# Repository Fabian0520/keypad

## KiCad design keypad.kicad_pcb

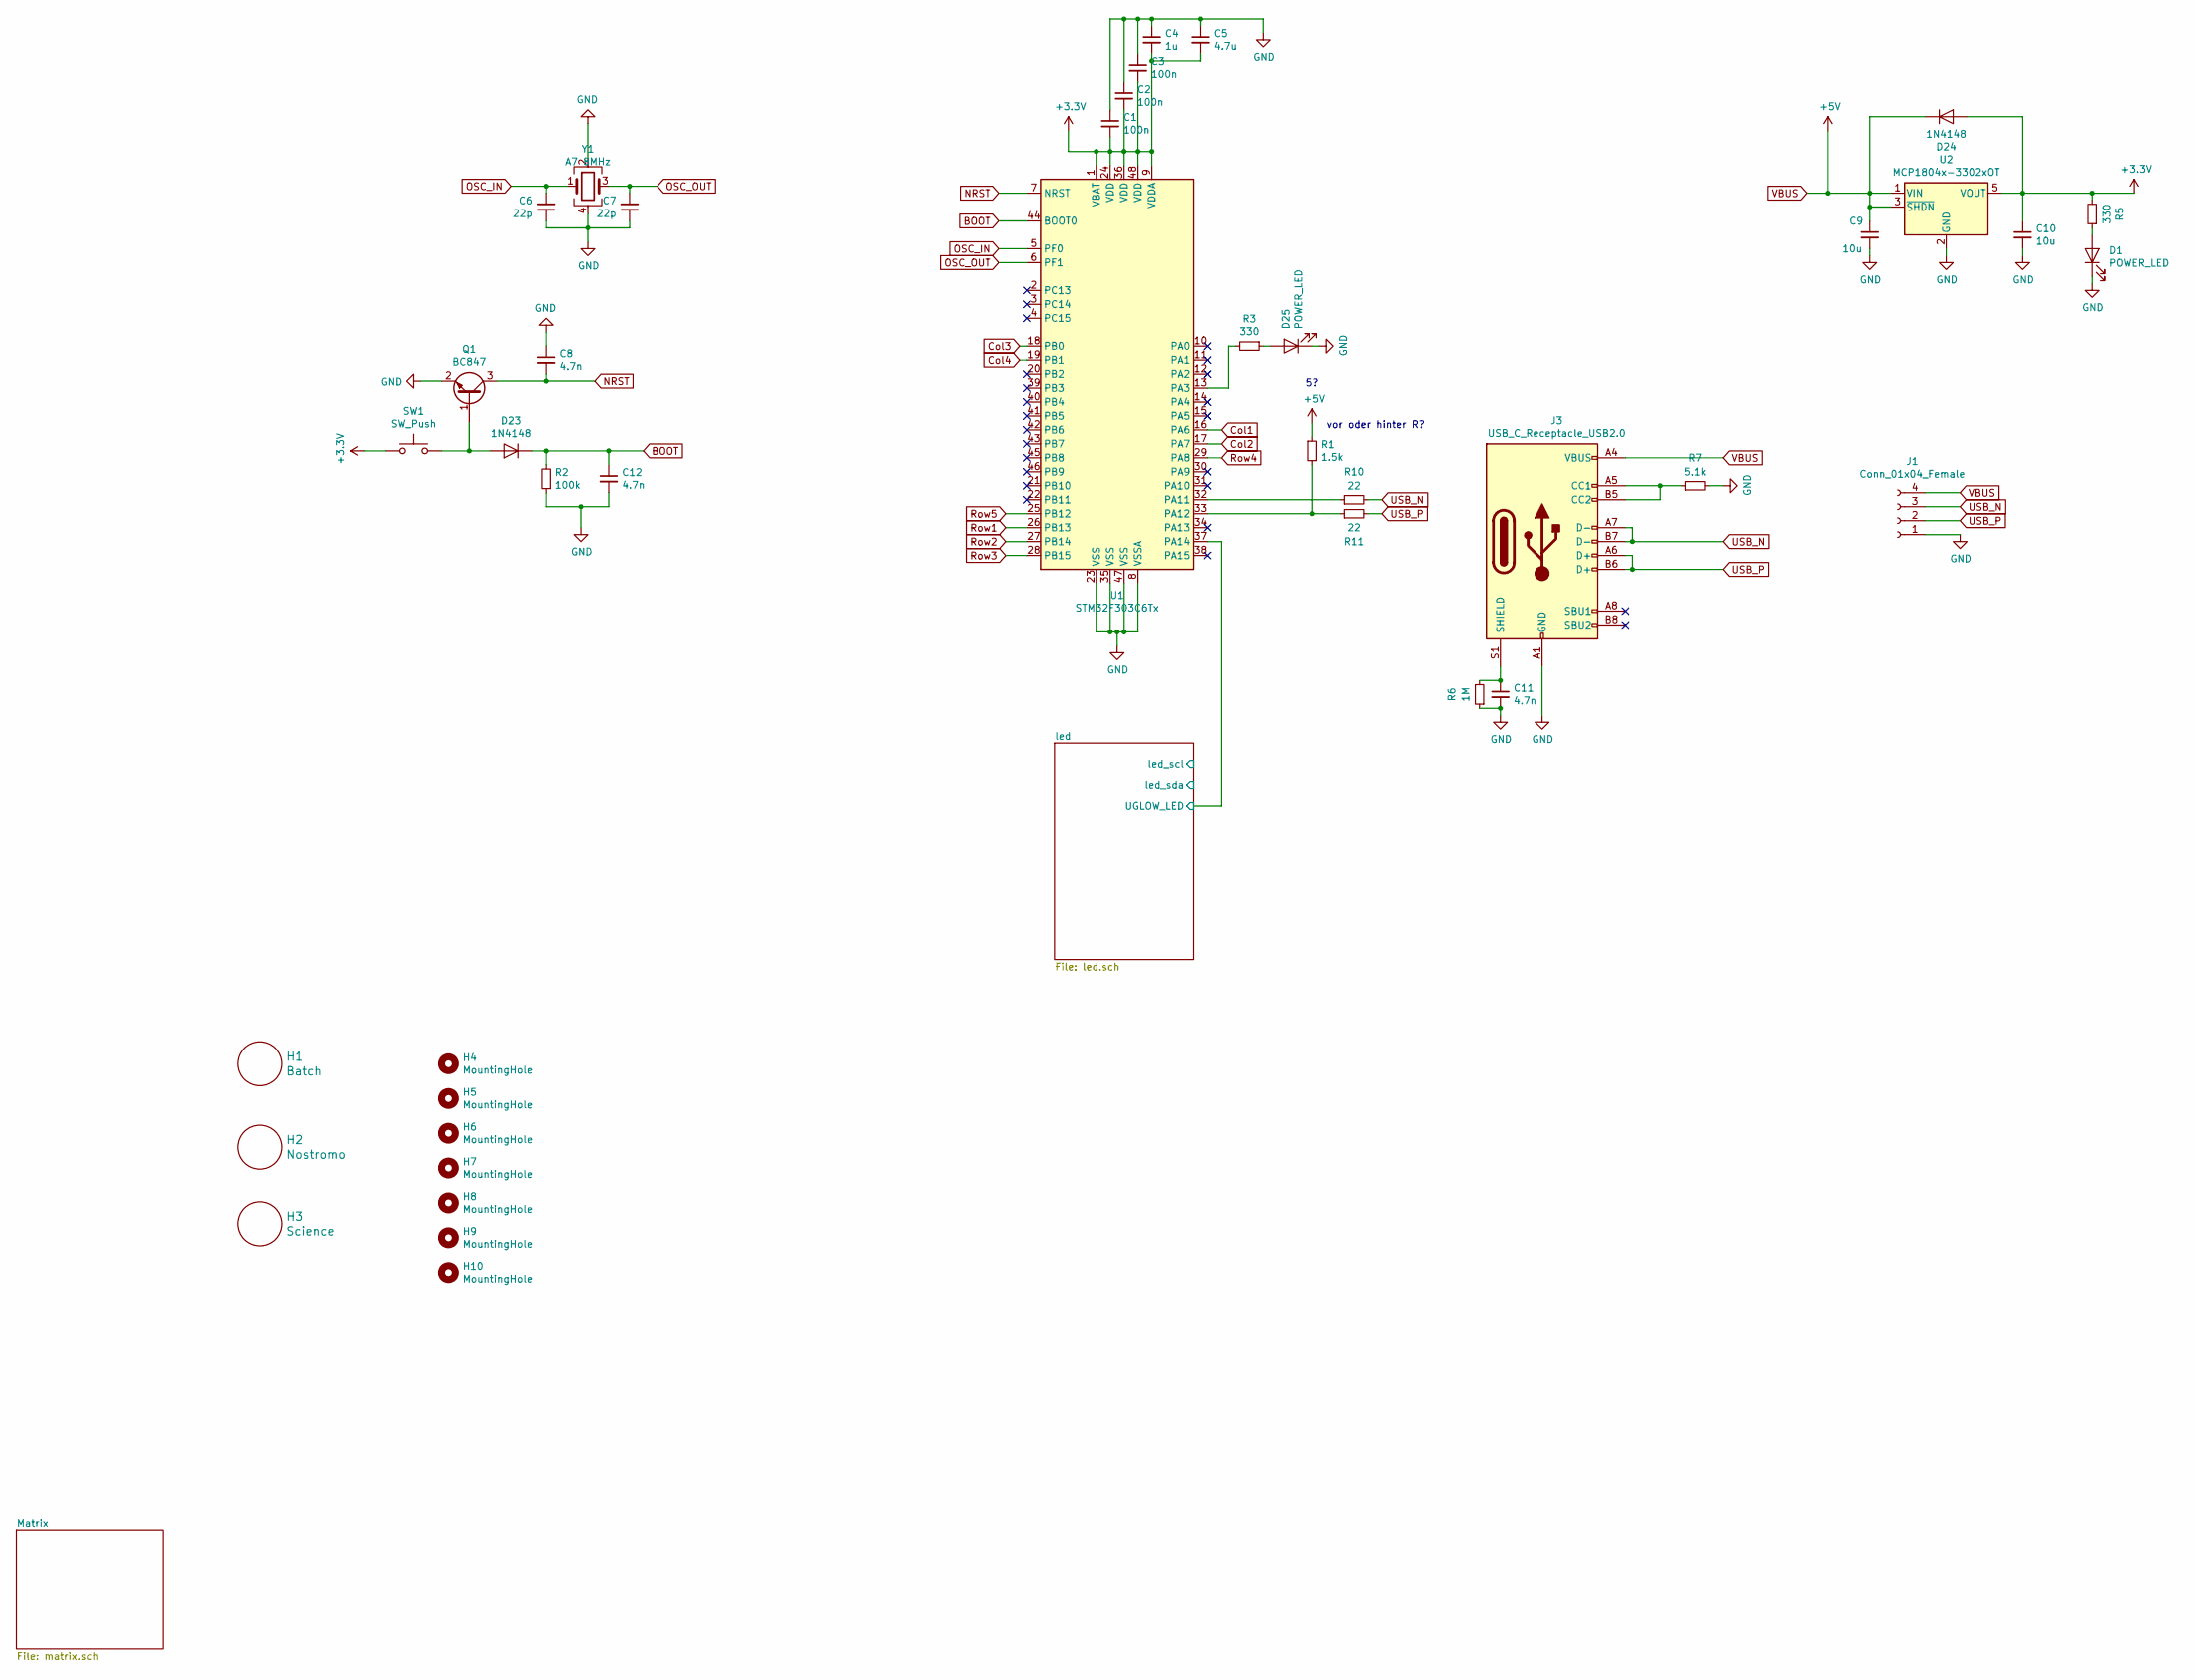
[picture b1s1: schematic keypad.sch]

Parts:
C1, C2, C3: 100n; C_0805_2012Metric_Pad1.15x1.40mm_HandSolder
C4: 1u; C_0805_2012Metric_Pad1.15x1.40mm_HandSolder
C5: 4.7u; C_0805_2012Metric_Pad1.15x1.40mm_HandSolder
C6, C7: 22p; C_0805_2012Metric_Pad1.15x1.40mm_HandSolder
C8, C11, C12: 4.7n; C_0805_2012Metric_Pad1.15x1.40mm_HandSolder
C9, C10: 10u; C_0805_2012Metric_Pad1.15x1.40mm_HandSolder
D1, D25: POWER_LED; LED_0805_2012Metric_Pad1.15x1.40mm_HandSolder
D23, D24: 1N4148; D_0805_2012Metric_Pad1.15x1.40mm_HandSolder
H1: Batch; nostromo_batch
H2: Nostromo; nostromo
H3: Science; science_badge
H4, H5, H6, H7, H8, H9, H10: MountingHole; MountingHole_2.2mm_M2
J1: Conn_01x04_Female; PinHeader_1x04_P2.00mm_Vertical
J3: USB_C_Receptacle_USB2.0; USB C HRQ low cost
Q1: BC847; SOT-23
R1: 1.5k; R_0805_2012Metric_Pad1.15x1.40mm_HandSolder
R2: 100k; R_0805_2012Metric_Pad1.15x1.40mm_HandSolder
R3, R5: 330; R_0805_2012Metric_Pad1.15x1.40mm_HandSolder
R6: 1M; R_0805_2012Metric_Pad1.15x1.40mm_HandSolder
R7: 5.1k; R_0805_2012Metric_Pad1.15x1.40mm_HandSolder
R10, R11: 22; R_0805_2012Metric_Pad1.15x1.40mm_HandSolder
SW1: SW_Push; SW_SPST_B3U-1000P
U1: STM32F303C6Tx; LQFP-48_7x7mm_P0.5mm
U2: MCP1804x-3302xOT; SOT-23-5_HandSoldering
Y1: A7 8MHz; Crystal_SMD_5032-4Pin_5.0x3.2mm

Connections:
+3V3: C1.2, C2.2, C3.2, C4.2, C5.2, C10.1, D24.2 (A), R5.2, SW1.1, U1.1 (VBAT), U1.9 (VDDA), U1.24 (VDD), U1.36 (VDD), U1.48 (VDD), U2.5 (VOUT)
/led/UGLOW_LED: U1.37 (PA14); also elsewhere on the board
BOOT: C12.1, D23.1 (K), R2.2, U1.44 (BOOT0)
Col1: U1.16 (PA6); also elsewhere on the board
Col2: U1.17 (PA7); also elsewhere on the board
Col3: U1.18 (PB0); also elsewhere on the board
Col4: U1.19 (PB1); also elsewhere on the board
GND: C1.1, C2.1, C3.1, C4.1, C5.1, C6.1, C7.1, C8.1, C9.2, C10.2, C11.2, C12.2, D1.1 (K), D25.1 (K), J1.1, J3.A1 (GND), J3.A12 (GND), J3.B1 (GND), J3.B12 (GND), Q1.2 (E), R2.1, R6.1, R7.2, U1.8 (VSSA), U1.23 (VSS), U1.35 (VSS), U1.47 (VSS), U2.2 (GND), Y1.2, Y1.4; also elsewhere on the board
NRST: C8.2, Q1.3 (C), U1.7 (NRST)
unnamed: C11.1, J3.S1 (SHIELD), R6.2
unnamed: D1.2 (A), R5.1
unnamed: D23.2 (A), Q1.1 (B), SW1.2
unnamed: D25.2 (A), R3.1
unnamed: J3.A5 (CC1), J3.B5 (CC2), R7.1
unnamed: R1.2, R11.1, U1.33 (PA12)
unnamed: R3.2, U1.13 (PA3)
unnamed: R10.1, U1.32 (PA11)
OSC_IN: C6.2, U1.5 (PF0), Y1.1
OSC_OUT: C7.2, U1.6 (PF1), Y1.3
Row1: U1.26 (PB13); also elsewhere on the board
Row2: U1.27 (PB14); also elsewhere on the board
Row3: U1.28 (PB15); also elsewhere on the board
Row4: U1.29 (PA8); also elsewhere on the board
Row5: U1.25 (PB12); also elsewhere on the board
USB_N: J1.3, J3.A7 (D-), J3.B7 (D-), R10.2
USB_P: J1.2, J3.A6 (D+), J3.B6 (D+), R11.2
VBUS: C9.1, D24.1 (K), J1.4, J3.A4 (VBUS), J3.A9 (VBUS), J3.B4 (VBUS), J3.B9 (VBUS), R1.1, U2.1 (VIN), U2.3 (~SHDN); also elsewhere on the board

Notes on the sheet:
vor oder hinter R?

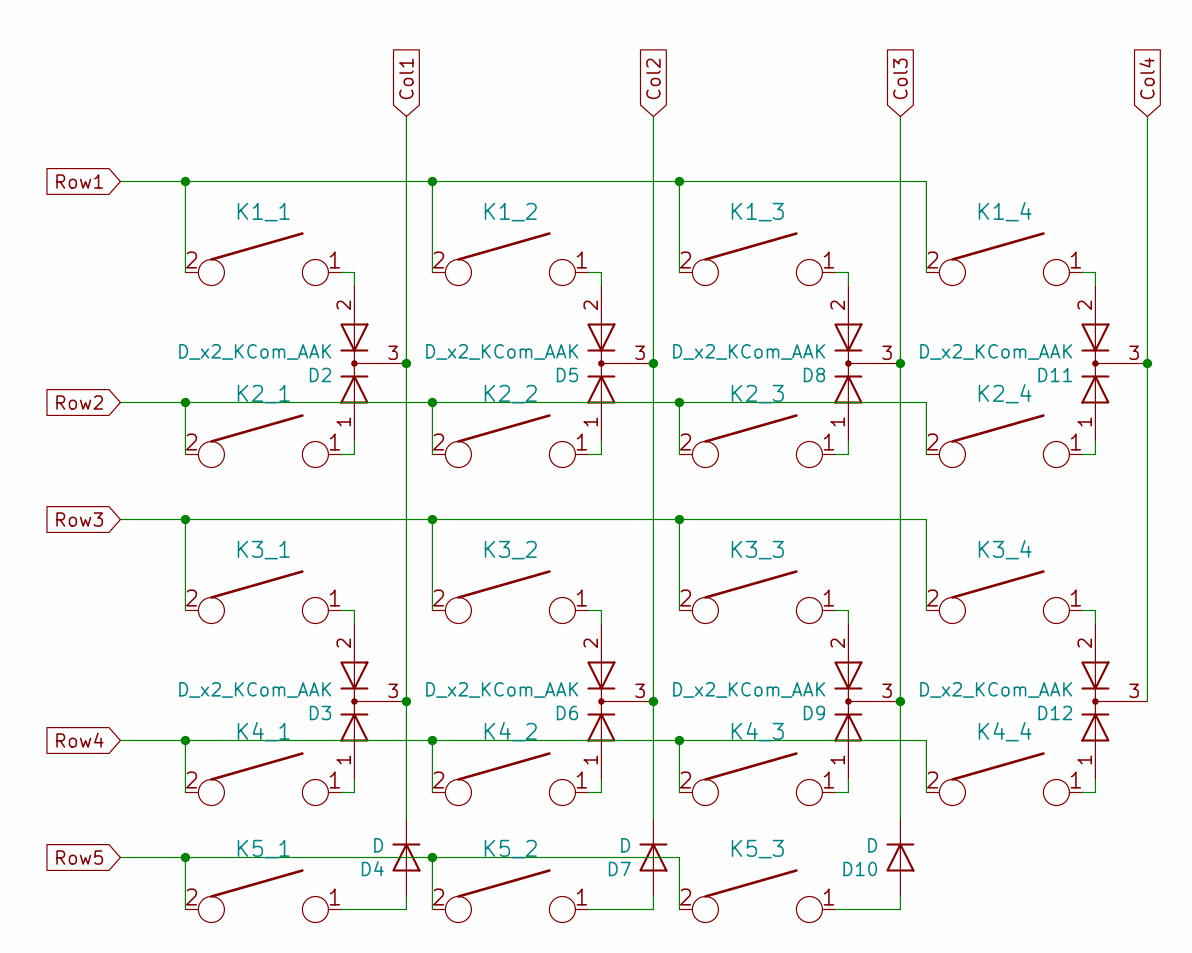
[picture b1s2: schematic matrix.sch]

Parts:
D2, D3, D5, D6, D8, D9, D11, D12: D_x2_KCom_AAK; SOT23-3_HSOL
D4, D7, D10: D; D_0805_2012Metric_Pad1.15x1.40mm_HandSolder
K1_1, K1_2, K1_3, K1_4, K2_1, K2_2, K2_3, K2_4, K3_1, K3_2, K3_3, K3_4, K4_1, K4_2, K4_3, K5_1, K5_2, K5_3: KEYSW; SW_Cherry_MX1A_1.00u_Plate
K4_4: KEYSW; SW_Cherry_MX1A_2.00u_PCB

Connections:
Col1: D2.3 (K), D3.3 (K), D4.1 (K); also elsewhere on the board
Col2: D5.3 (K), D6.3 (K), D7.1 (K); also elsewhere on the board
Col3: D8.3 (K), D9.3 (K), D10.1 (K); also elsewhere on the board
Col4: D11.3 (K), D12.3 (K); also elsewhere on the board
unnamed: D2.1 (A), K2_1.1
unnamed: D2.2 (A), K1_1.1
unnamed: D3.1 (A), K4_1.1
unnamed: D3.2 (A), K3_1.1
unnamed: D4.2 (A), K5_1.1
unnamed: D5.1 (A), K2_2.1
unnamed: D5.2 (A), K1_2.1
unnamed: D6.1 (A), K4_2.1
unnamed: D6.2 (A), K3_2.1
unnamed: D7.2 (A), K5_2.1
unnamed: D8.1 (A), K2_3.1
unnamed: D8.2 (A), K1_3.1
unnamed: D9.1 (A), K4_3.1
unnamed: D9.2 (A), K3_3.1
unnamed: D10.2 (A), K5_3.1
unnamed: D11.1 (A), K2_4.1
unnamed: D11.2 (A), K1_4.1
unnamed: D12.1 (A), K4_4.1
unnamed: D12.2 (A), K3_4.1
Row1: K1_1.2, K1_2.2, K1_3.2, K1_4.2; also elsewhere on the board
Row2: K2_1.2, K2_2.2, K2_3.2, K2_4.2; also elsewhere on the board
Row3: K3_1.2, K3_2.2, K3_3.2, K3_4.2; also elsewhere on the board
Row4: K4_1.2, K4_2.2, K4_3.2, K4_4.2; also elsewhere on the board
Row5: K5_1.2, K5_2.2, K5_3.2; also elsewhere on the board

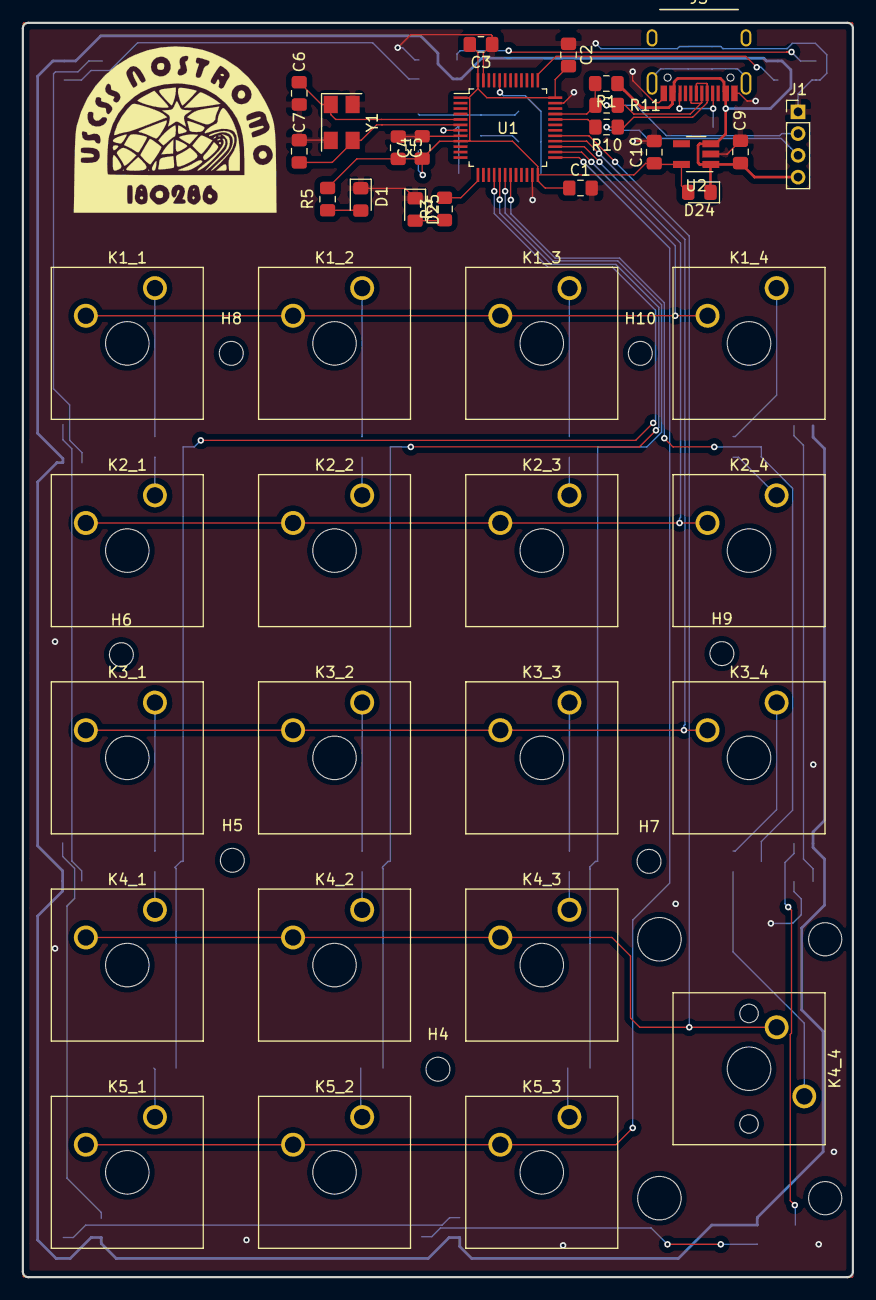
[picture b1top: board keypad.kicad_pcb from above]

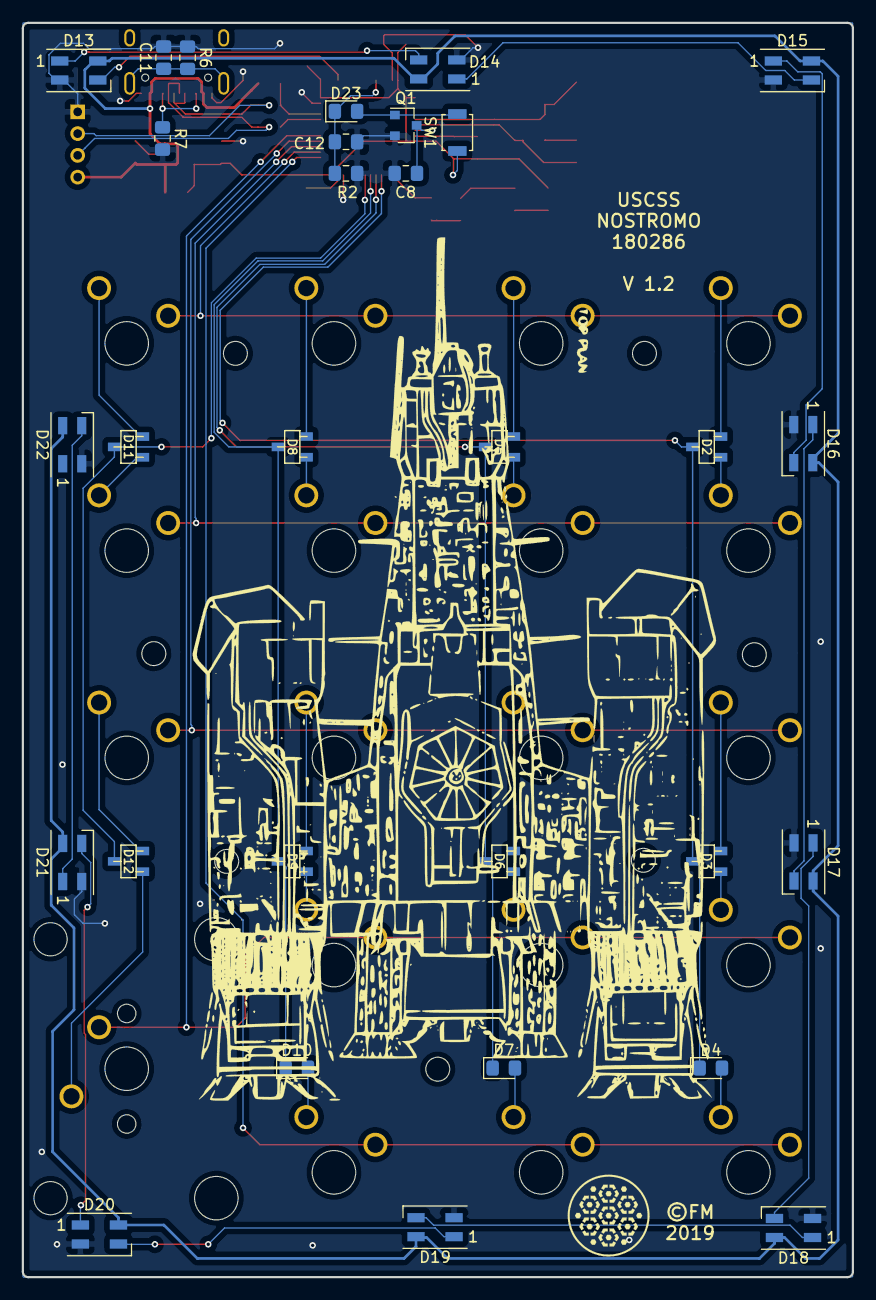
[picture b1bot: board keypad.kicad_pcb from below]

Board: 2 copper layers, 76.3 x 115.3 mm, 81 parts (32 on the bottom side), 55 nets.

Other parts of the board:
D13, D14, D15, D16, D17, D18, D19, D20, D21, D22: SK6805; LED_SK6812MINI_PLCC4_3.5x3.5mm_P1.75mm

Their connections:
/led/UGLOW_LED: D13.3; also elsewhere on the board
GND: D13.2, D14.2, D15.2, D16.2, D17.2, D18.2, D19.2, D20.2, D21.2, D22.2; also elsewhere on the board
unnamed: D13.1, D14.3
unnamed: D14.1, D15.3
unnamed: D15.1, D16.3
unnamed: D16.1, D17.3
unnamed: D17.1, D18.3
unnamed: D18.1, D19.3
unnamed: D19.1, D20.3
unnamed: D20.1, D21.3
unnamed: D21.1, D22.3
VBUS: D13.4, D14.4, D15.4, D16.4, D17.4, D18.4, D19.4, D20.4, D21.4, D22.4; also elsewhere on the board

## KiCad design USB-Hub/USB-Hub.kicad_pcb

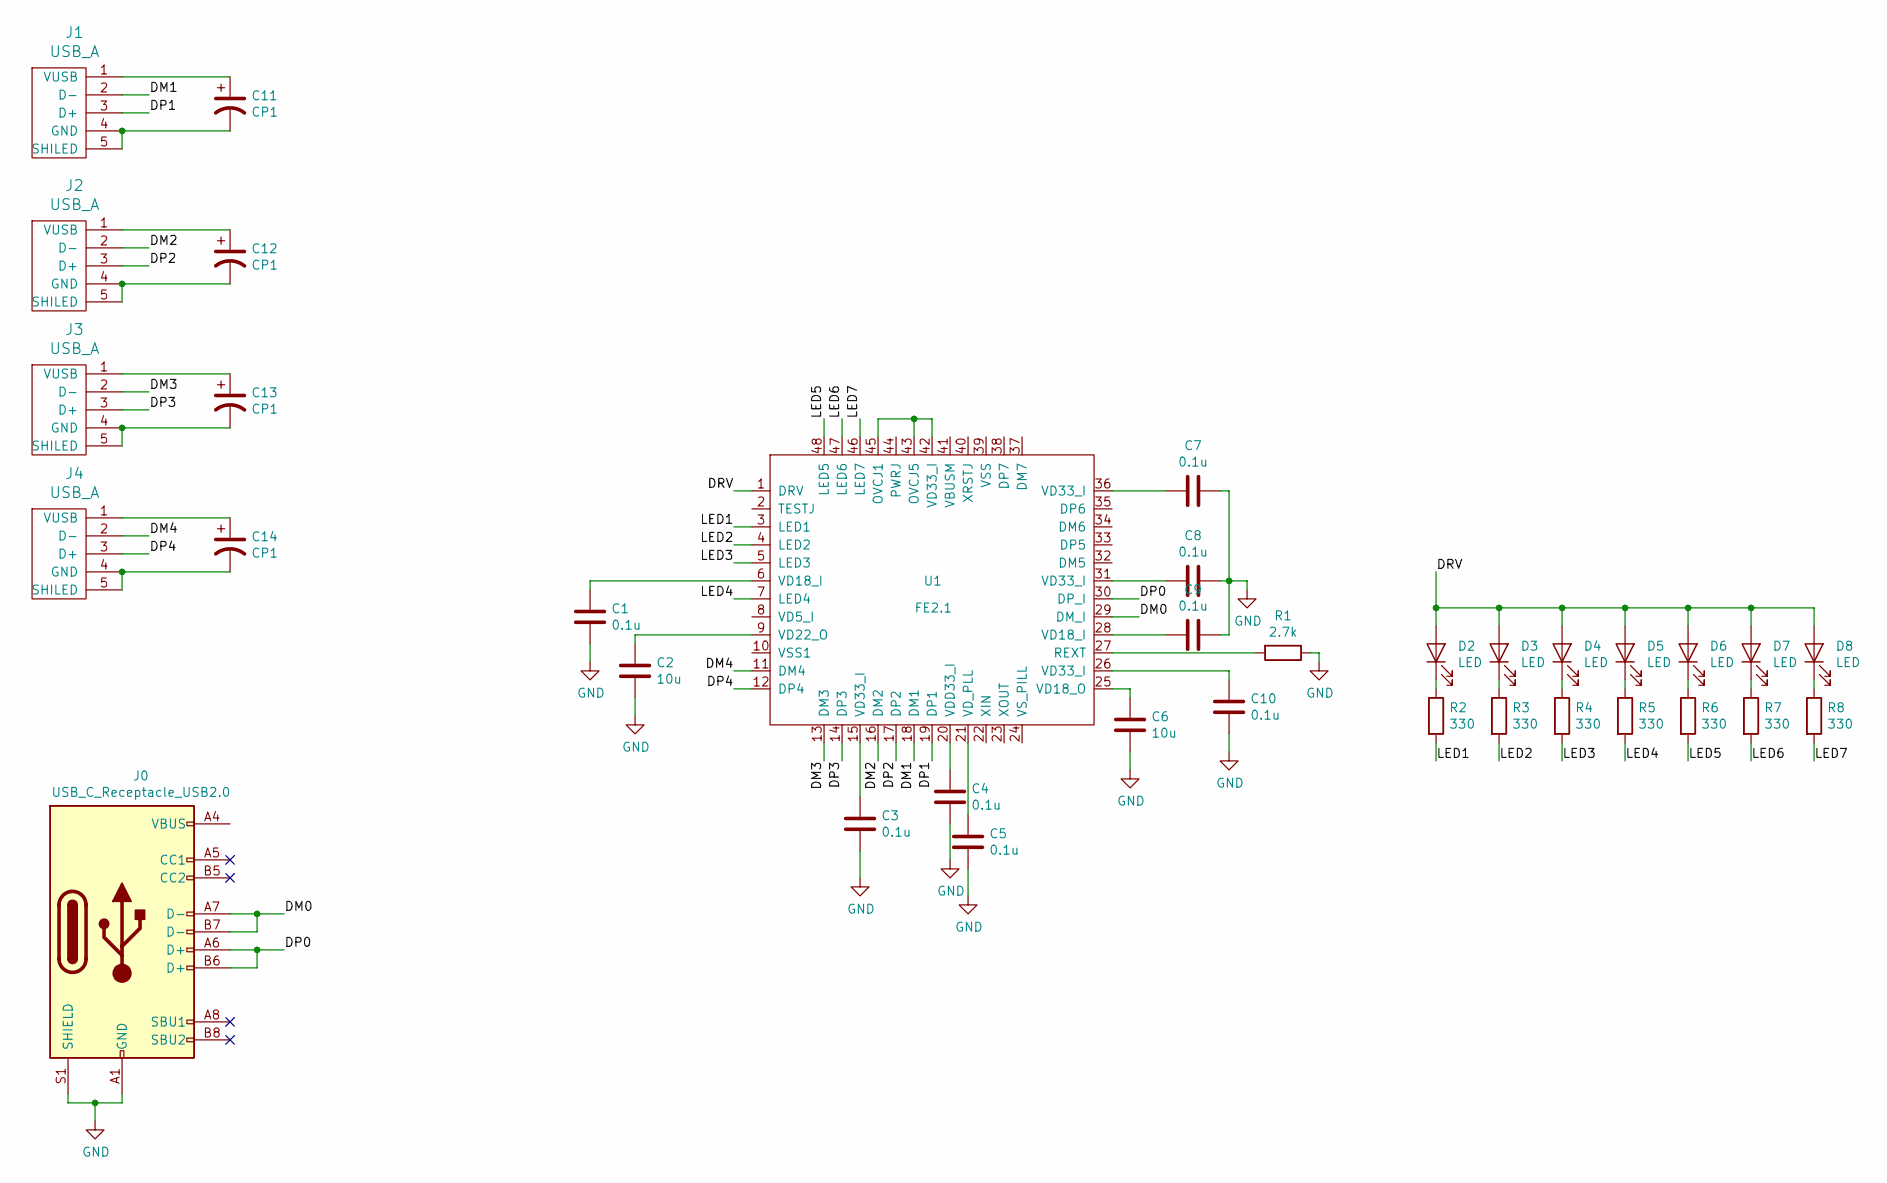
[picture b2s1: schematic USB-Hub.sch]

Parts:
C1, C3, C4, C5, C7, C8, C9, C10: 0.1u; C_0805_2012Metric_Pad1.15x1.40mm_HandSolder
C2, C6: 10u; C_0805_2012Metric_Pad1.15x1.40mm_HandSolder
C11, C12, C13, C14: CP1; C_0603_1608Metric_Pad1.05x0.95mm_HandSolder
D2, D3, D4, D5, D6, D7, D8: LED; LED_0603_1608Metric_Pad1.05x0.95mm_HandSolder
J0: USB_C_Receptacle_USB2.0; USB_C_Receptacle_Amphenol_12401548E4-2A
J1, J2, J3, J4: USB_A
R1: 2.7k; R_0805_2012Metric_Pad1.15x1.40mm_HandSolder
R2, R3, R4, R5, R6, R7, R8: 330; R_0805_2012Metric_Pad1.15x1.40mm_HandSolder
U1: FE2.1; LQFP-48_7x7mm_P0.5mm

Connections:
/DM0: J0.A7 (D-), J0.B7 (D-), U1.29 (DM_I)
/DM1: J1.2 (D-), U1.18 (DM1)
/DM2: J2.2 (D-), U1.16 (DM2)
/DM3: J3.2 (D-), U1.13 (DM3)
/DM4: J4.2 (D-), U1.11 (DM4)
/DP0: J0.A6 (D+), J0.B6 (D+), U1.30 (DP_I)
/DP1: J1.3 (D+), U1.19 (DP1)
/DP2: J2.3 (D+), U1.17 (DP2)
/DP3: J3.3 (D+), U1.14 (DP3)
/DP4: J4.3 (D+), U1.12 (DP4)
/DRV: D2.2 (A), D3.2 (A), D4.2 (A), D5.2 (A), D6.2 (A), D7.2 (A), D8.2 (A), U1.1 (DRV)
/LED1: R2.2, U1.3 (LED1)
/LED2: R3.2, U1.4 (LED2)
/LED3: R4.2, U1.5 (LED3)
/LED4: R5.2, U1.7 (LED4)
/LED5: R6.2, U1.48 (LED5)
/LED6: R7.2, U1.47 (LED6)
/LED7: R8.2, U1.46 (LED7)
GND: C1.2, C2.2, C3.2, C4.2, C5.2, C6.2, C7.1, C8.2, C9.2, C10.2, J0.A1 (GND), J0.A12 (GND), J0.B1 (GND), J0.B12 (GND), J0.S1 (SHIELD), R1.1
unnamed: C1.1, U1.6 (VD18_I)
unnamed: C2.1, U1.9 (VD22_O)
unnamed: C3.1, U1.15 (VD33_I)
unnamed: C4.1, U1.20 (VDD33_I)
unnamed: C5.1, U1.21 (VD_PLL)
unnamed: C6.1, U1.25 (VD18_O)
unnamed: C7.2, U1.36 (VD33_I)
unnamed: C8.1, U1.31 (VD33_I)
unnamed: C9.1, U1.28 (VD18_I)
unnamed: C10.1, U1.26 (VD33_I)
unnamed: C11.1, J1.1 (VUSB)
unnamed: C11.2, J1.4 (GND), J1.5 (SHILED)
unnamed: C12.1, J2.1 (VUSB)
unnamed: C12.2, J2.4 (GND), J2.5 (SHILED)
unnamed: C13.1, J3.1 (VUSB)
unnamed: C13.2, J3.4 (GND), J3.5 (SHILED)
unnamed: C14.1, J4.1 (VUSB)
unnamed: C14.2, J4.4 (GND), J4.5 (SHILED)
unnamed: D2.1 (K), R2.1
unnamed: D3.1 (K), R3.1
unnamed: D4.1 (K), R4.1
unnamed: D5.1 (K), R5.1
unnamed: D6.1 (K), R6.1
unnamed: D7.1 (K), R7.1
unnamed: D8.1 (K), R8.1
unnamed: R1.2, U1.27 (REXT)
unnamed: U1.42 (VD33_I), U1.43 (OVCJ5), U1.45 (OVCJ1)
VBUS: J0.A4 (VBUS), J0.A9 (VBUS), J0.B4 (VBUS), J0.B9 (VBUS)

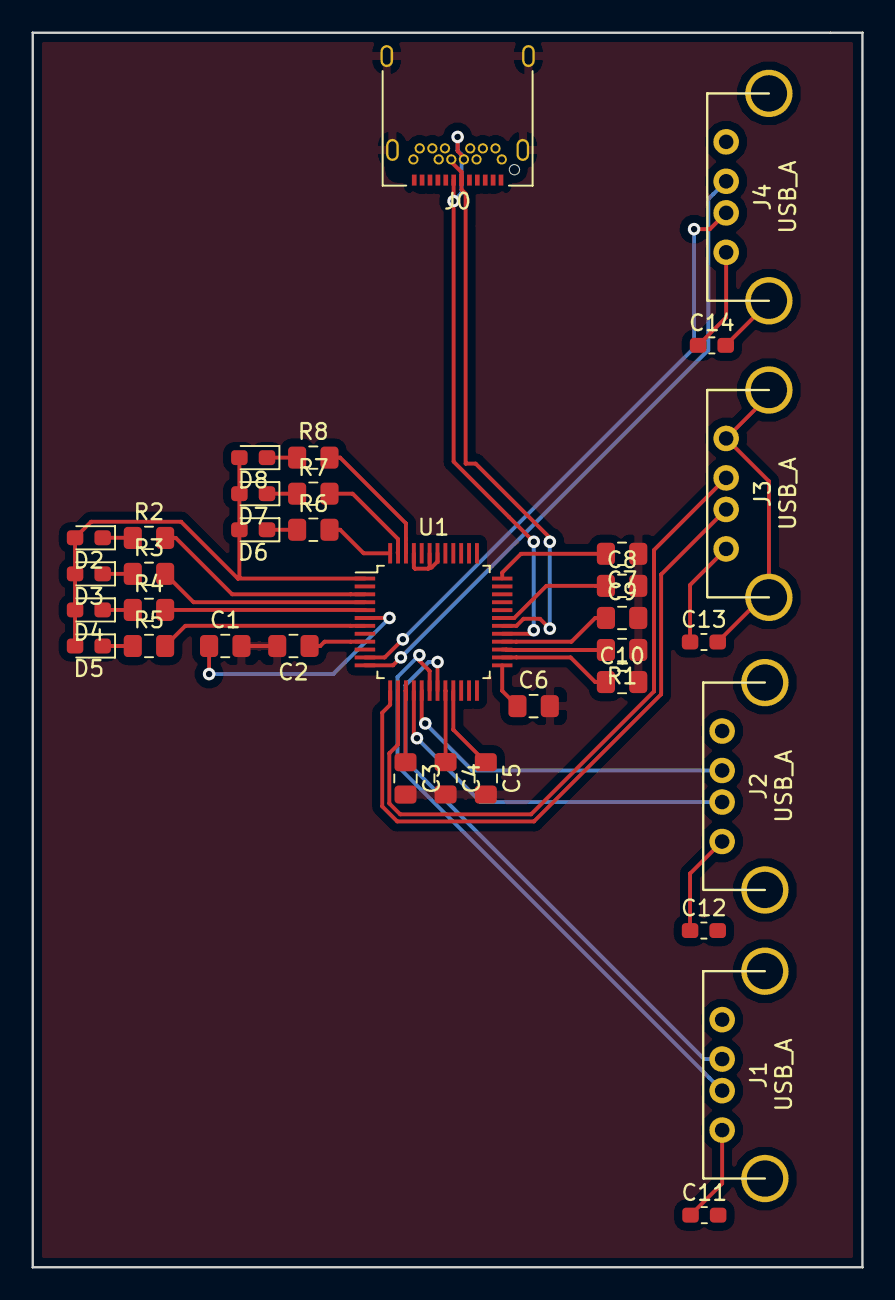
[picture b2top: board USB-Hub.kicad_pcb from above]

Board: 2 copper layers, 52.6 x 78.2 mm, 35 parts (0 on the bottom side), 47 nets.

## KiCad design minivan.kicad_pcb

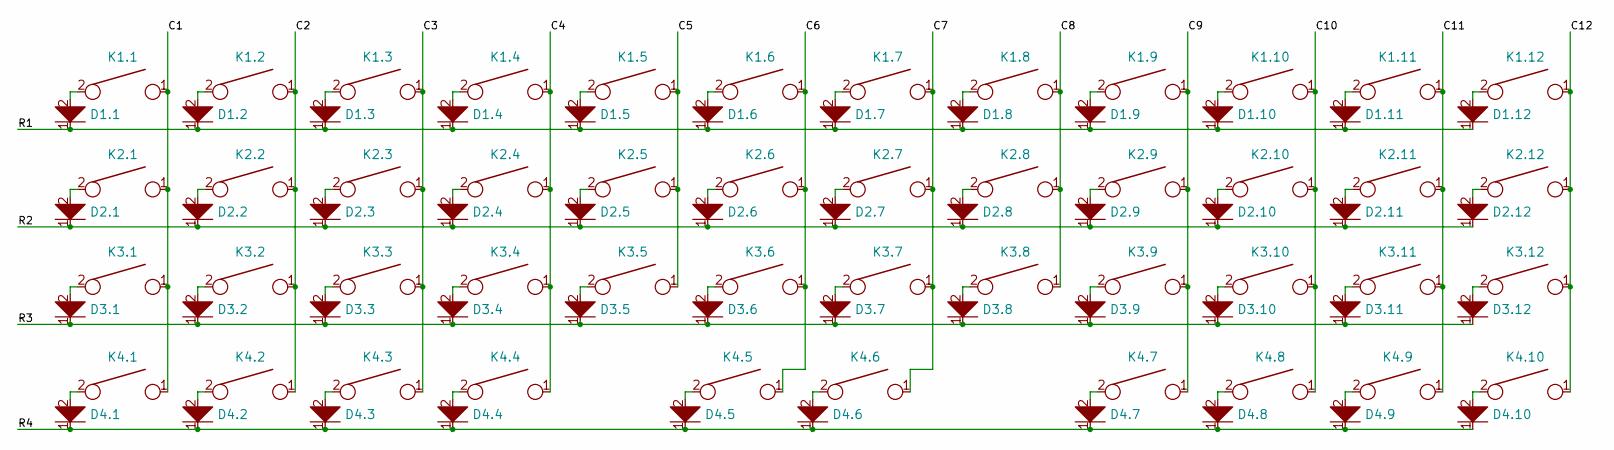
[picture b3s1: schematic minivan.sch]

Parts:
D1.1, D1.2, D1.3, D1.4, D1.5, D1.6, D1.7, D1.8, D1.9, D1.10, D1.11, D1.12, D2.1, D2.2, D2.3, D2.4, D2.5, D2.6, D2.7, D2.8, D2.9, D2.10, D2.11, D2.12, D3.1, D3.2, D3.3, D3.4, D3.5, D3.6, D3.7, D3.8, D3.9, D3.10, D3.11, D3.12, D4.1, D4.2, D4.3, D4.4, D4.5, D4.6, D4.7, D4.8, D4.9, D4.10: D; D_SOD123_axial
K1.1, K1.2, K1.3, K1.4, K1.5, K1.6, K1.7, K1.8, K1.9, K1.10, K1.11, K2.2, K2.3, K2.4, K2.5, K2.6, K2.7, K2.8, K2.9, K2.10, K2.11, K3.2, K3.3, K3.4, K3.5, K3.6, K3.7, K3.8, K3.9, K3.10, K3.11, K3.12, K4.1, K4.2, K4.3, K4.8, K4.9, K4.10: KEYSW; SW_Cherry_MX1A_1.00u_PCB
K1.12, K3.1: KEYSW; SW_Cherry_MX1A_1.75u_PCB
K2.1, K4.4, K4.7: KEYSW; SW_Cherry_MX1A_1.25u_PCB
K2.12: KEYSW; SW_Cherry_MX1A_1.50u_PCB
K4.5: KEYSW; SW_Cherry_MX1A_2.25u_PCB
K4.6: KEYSW; SW_Cherry_MX1A_2.00u_PCB

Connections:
/C1: K1.1.1, K2.1.1, K3.1.1, K4.1.1
/C2: K1.2.1, K2.2.1, K3.2.1, K4.2.1
/C3: K1.3.1, K2.3.1, K3.3.1, K4.3.1
/C4: K1.4.1, K2.4.1, K3.4.1, K4.4.1
/C5: K1.5.1, K2.5.1, K3.5.1
/C6: K1.6.1, K2.6.1, K3.6.1, K4.5.1
/C7: K1.7.1, K2.7.1, K3.7.1, K4.6.1
/C8: K1.8.1, K2.8.1, K3.8.1
/C9: K1.9.1, K2.9.1, K3.9.1, K4.7.1
/C10: K1.10.1, K2.10.1, K3.10.1, K4.8.1
/C11: K1.11.1, K2.11.1, K3.11.1, K4.9.1
/C12: K1.12.1, K2.12.1, K3.12.1, K4.10.1
/R1: D1.1.1, D1.2.1, D1.3.1, D1.4.1, D1.5.1, D1.6.1, D1.7.1, D1.8.1, D1.9.1, D1.10.1, D1.11.1, D1.12.1
/R2: D2.1.1, D2.2.1, D2.3.1, D2.4.1, D2.5.1, D2.6.1, D2.7.1, D2.8.1, D2.9.1, D2.10.1, D2.11.1, D2.12.1
/R3: D3.1.1, D3.2.1, D3.3.1, D3.4.1, D3.5.1, D3.6.1, D3.7.1, D3.8.1, D3.9.1, D3.10.1, D3.11.1, D3.12.1
/R4: D4.1.1, D4.2.1, D4.3.1, D4.4.1, D4.5.1, D4.6.1, D4.7.1, D4.8.1, D4.9.1, D4.10.1
unnamed: D1.1.2, K1.1.2
unnamed: D1.2.2, K1.2.2
unnamed: D1.3.2, K1.3.2
unnamed: D1.4.2, K1.4.2
unnamed: D1.5.2, K1.5.2
unnamed: D1.6.2, K1.6.2
unnamed: D1.7.2, K1.7.2
unnamed: D1.8.2, K1.8.2
unnamed: D1.9.2, K1.9.2
unnamed: D1.10.2, K1.10.2
unnamed: D1.11.2, K1.11.2
unnamed: D1.12.2, K1.12.2
unnamed: D2.1.2, K2.1.2
unnamed: D2.2.2, K2.2.2
unnamed: D2.3.2, K2.3.2
unnamed: D2.4.2, K2.4.2
unnamed: D2.5.2, K2.5.2
unnamed: D2.6.2, K2.6.2
unnamed: D2.7.2, K2.7.2
unnamed: D2.8.2, K2.8.2
unnamed: D2.9.2, K2.9.2
unnamed: D2.10.2, K2.10.2
unnamed: D2.11.2, K2.11.2
unnamed: D2.12.2, K2.12.2
unnamed: D3.1.2, K3.1.2
unnamed: D3.2.2, K3.2.2
unnamed: D3.3.2, K3.3.2
unnamed: D3.4.2, K3.4.2
unnamed: D3.5.2, K3.5.2
unnamed: D3.6.2, K3.6.2
unnamed: D3.7.2, K3.7.2
unnamed: D3.8.2, K3.8.2
unnamed: D3.9.2, K3.9.2
unnamed: D3.10.2, K3.10.2
unnamed: D3.11.2, K3.11.2
unnamed: D3.12.2, K3.12.2
unnamed: D4.1.2, K4.1.2
unnamed: D4.2.2, K4.2.2
unnamed: D4.3.2, K4.3.2
unnamed: D4.4.2, K4.4.2
unnamed: D4.5.2, K4.5.2
unnamed: D4.6.2, K4.6.2
unnamed: D4.7.2, K4.7.2
unnamed: D4.8.2, K4.8.2
unnamed: D4.9.2, K4.9.2
unnamed: D4.10.2, K4.10.2

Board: 2 copper layers, 92 parts (0 on the bottom side), 62 nets, no tracks yet.

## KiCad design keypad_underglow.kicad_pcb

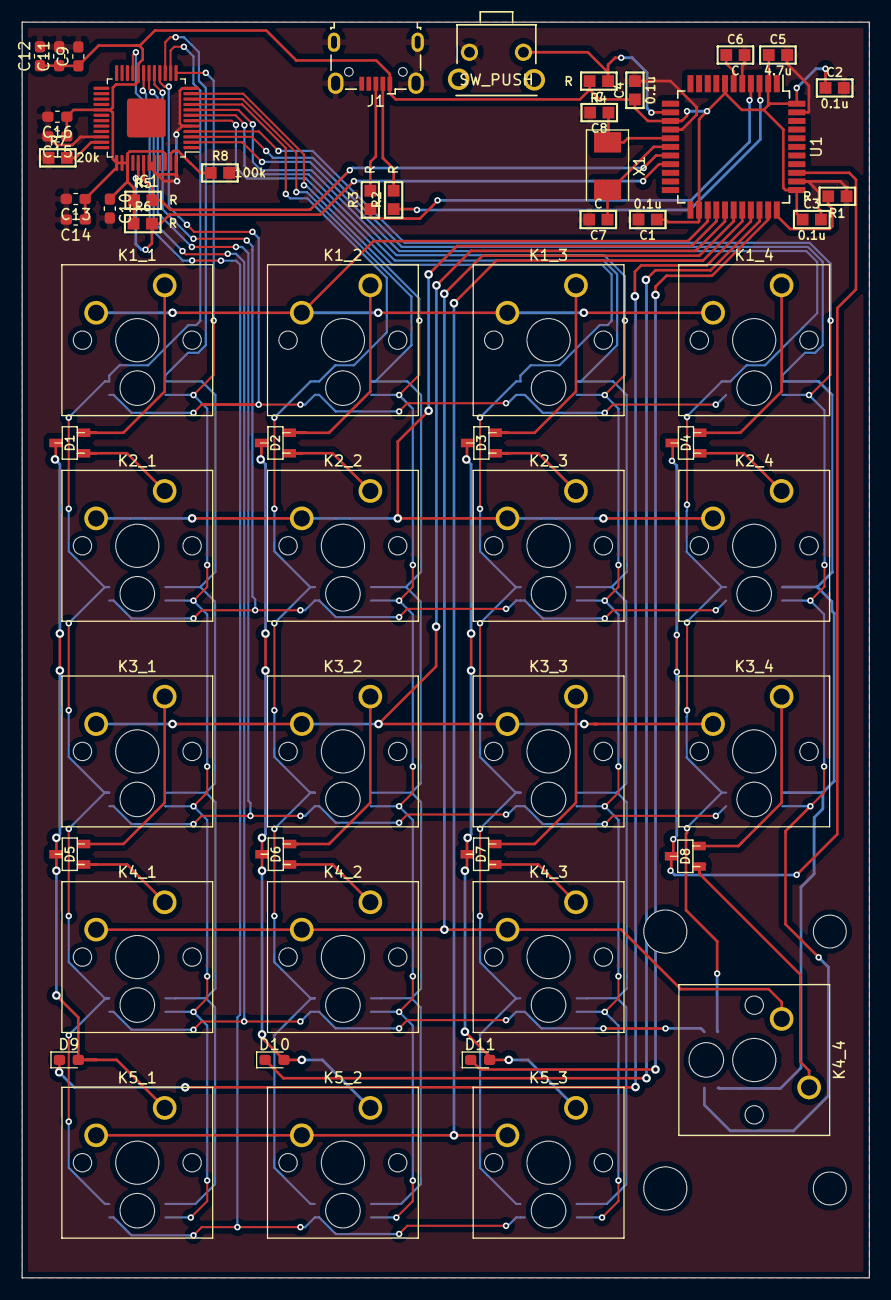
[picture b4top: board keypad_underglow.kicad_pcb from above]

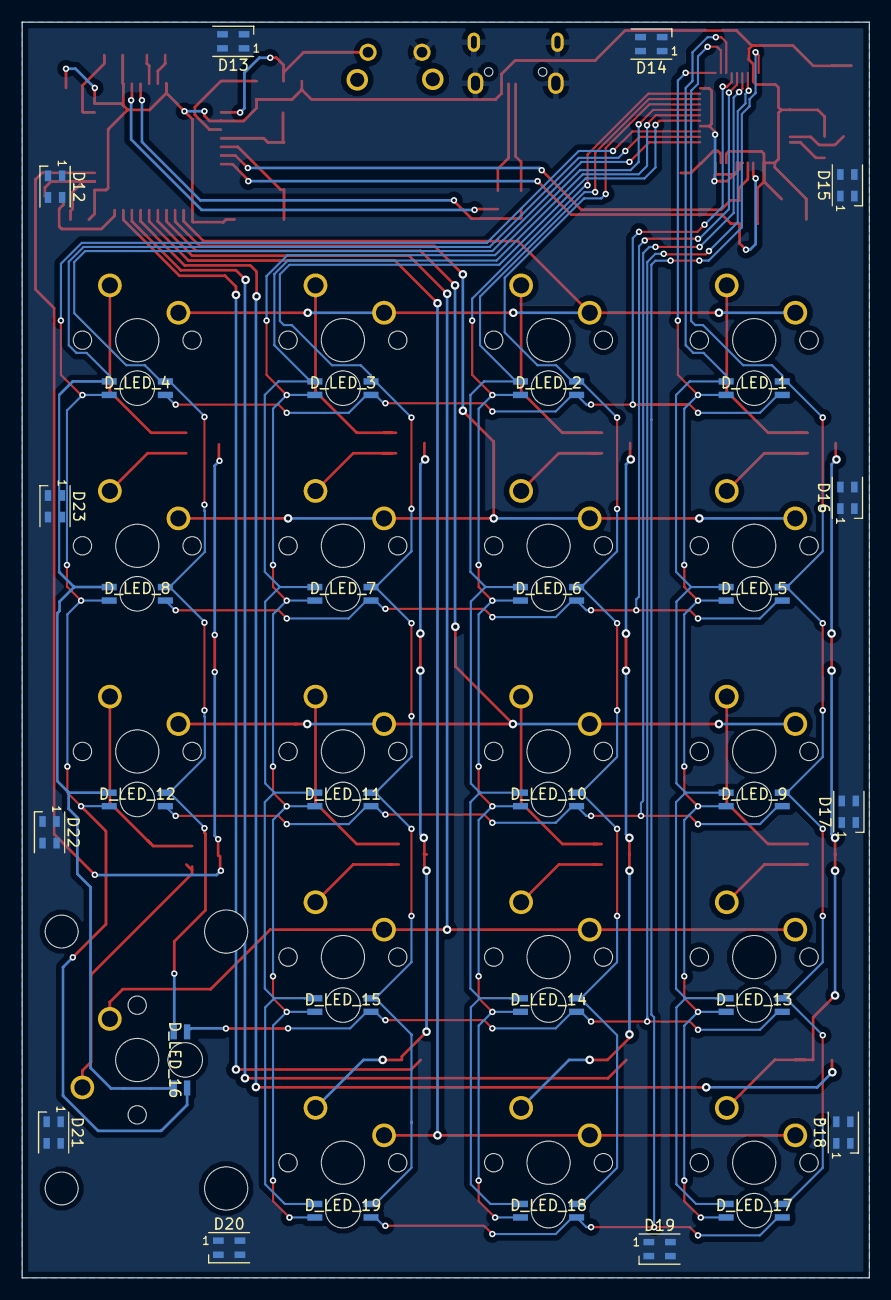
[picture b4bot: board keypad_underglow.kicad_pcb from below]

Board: 2 copper layers, 78.5 x 116.3 mm, 90 parts (31 on the bottom side), 71 nets.

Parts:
C1, C2, C3, C4: 0.1u; C_1608
C5: 4.7u; C_1608
C6, C7, C8: C; C_1608
C9, C13, C15: 0.1uF; C_0603_1608Metric_Pad1.05x0.95mm_HandSolder
C10: C; C_0603_1608Metric_Pad1.05x0.95mm_HandSolder
C11, C14, C16: 0.47uF; C_0603_1608Metric_Pad1.05x0.95mm_HandSolder
C12: 22uF; C_0603_1608Metric_Pad1.05x0.95mm_HandSolder
D1, D2, D3, D4, D5, D6, D7, D8: D_x2_KCom_AAK; SOT23-3_HSOL
D9, D10, D11: D; D_0603_1608Metric_Pad1.05x0.95mm_HandSolder
D12, D13, D14, D15, D16, D17, D18, D19, D20, D21, D22, D23: SK6805; LED_SK6805_PLCC4_2.4x2.7mm_P1.3mm
D_LED_1, D_LED_2, D_LED_3, D_LED_4, D_LED_5, D_LED_6, D_LED_7, D_LED_8, D_LED_9, D_LED_10, D_LED_11, D_LED_12, D_LED_13, D_LED_14, D_LED_15, D_LED_16, D_LED_17, D_LED_18, D_LED_19: LED_RABG; reverse_RGB_LED
IC1: IS31FL3733-TQLS4; LQFP-48-1EP_7x7mm_P0.5mm_EP3.6x3.6mm
J1: USB_mini_micro_B; USB_Micro-B_Wuerth_629105150521
K1_1, K1_2, K1_3, K1_4, K2_1, K2_2, K2_3, K2_4, K3_1, K3_2, K3_3, K3_4, K4_1, K4_2, K4_3, K5_1, K5_2, K5_3: KEYSW; SW_Cherry_MX1A_1.00u_PCB
K4_4: KEYSW; SW_Cherry_MX1A_2.00u_PCB
R1, R2, R3, R4, R5, R6: R; R_1608
R7: 20k; R_1608
R8: 100k; R_1608
SW1: SW_PUSH; SW_TACT_TH_HORIZ_LOW
U1: ATMEGA32U4; LQFP-44_10x10mm_P0.8mm
X1: XTAL_GND; Crystal_SMD_0603-2Pin_6.0x3.5mm

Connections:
/led/CS1: D_LED_1.2, D_LED_2.2, D_LED_3.2, D_LED_4.2, IC1.16
/led/CS2: D_LED_5.2, D_LED_6.2, D_LED_7.2, D_LED_8.2, IC1.17
/led/CS3: D_LED_9.2, D_LED_10.2, D_LED_11.2, D_LED_12.2, IC1.18
/led/CS4: D_LED_13.2, D_LED_14.2, D_LED_15.2, D_LED_16.2, IC1.19
/led/CS5: D_LED_17.2, D_LED_18.2, D_LED_19.2, IC1.21
/led/SW1: D_LED_4.3, D_LED_8.3, D_LED_12.3, D_LED_16.3, IC1.2
/led/SW2: D_LED_4.4, D_LED_8.4, D_LED_12.4, D_LED_16.4, IC1.3
/led/SW3: D_LED_4.1, D_LED_8.1, D_LED_12.1, D_LED_16.1, IC1.4
/led/SW4: D_LED_3.3, D_LED_7.3, D_LED_11.3, D_LED_15.3, D_LED_19.3, IC1.6
/led/SW5: D_LED_3.4, D_LED_7.4, D_LED_11.4, D_LED_15.4, D_LED_19.4, IC1.7
/led/SW6: D_LED_3.1, D_LED_7.1, D_LED_11.1, D_LED_15.1, D_LED_19.1, IC1.8
/led/SW7: D_LED_2.3, D_LED_6.3, D_LED_10.3, D_LED_14.3, D_LED_18.3, IC1.9
/led/SW8: D_LED_2.4, D_LED_6.4, D_LED_10.4, D_LED_14.4, D_LED_18.4, IC1.10
/led/SW9: D_LED_2.1, D_LED_6.1, D_LED_10.1, D_LED_14.1, D_LED_18.1, IC1.11
/led/SW10: D_LED_1.3, D_LED_5.3, D_LED_9.3, D_LED_13.3, D_LED_17.3, IC1.14
/led/SW11: D_LED_1.4, D_LED_5.4, D_LED_9.4, D_LED_13.4, D_LED_17.4, IC1.15
/led/SW12: D_LED_1.1, D_LED_5.1, D_LED_9.1, D_LED_13.1, D_LED_17.1, IC1.13
/led/UGLOW_LED: D12.3, U1.1
/led/led_scl: IC1.42, R5.2, U1.18
/led/led_sda: IC1.41, R6.2, U1.19
Col1: D9.1, U1.30
Col2: D10.1, U1.31
Col3: D11.1, U1.32
Col4: D4.3, D8.3, U1.36
GND: C1.2, C2.2, C3.2, C4.2, C5.2, C6.2, C7.2, C8.2, C9.2, C10.2, C11.2, C12.2, C13.2, C14.2, C15.2, C16.2, D12.2, D14.2, D16.2, D18.2, D20.2, D22.2, IC1.5, IC1.12, IC1.34, IC1.43, IC1.44, IC1.48, J1.5, J1.6, R1.1, R7.1, R8.2, SW1.1, U1.5, U1.15, U1.23, U1.35, U1.43
unnamed: C6.1, U1.6
unnamed: C7.1, U1.17, X1.2
unnamed: C8.1, U1.16, X1.1
unnamed: D1.1, K2_1.1
unnamed: D1.2, K1_1.1
unnamed: D1.3, D5.3, D9.2, K5_1.1
unnamed: D2.1, K2_2.1
unnamed: D2.2, K1_2.1
unnamed: D3.1, K2_3.1
unnamed: D3.2, K1_3.1
unnamed: D4.1, K2_4.1
unnamed: D4.2, K1_4.1
unnamed: D5.1, K4_1.1
unnamed: D5.2, K3_1.1
unnamed: D6.1, K4_2.1
unnamed: D6.2, K3_2.1
unnamed: D7.1, K4_3.1
unnamed: D7.2, K3_3.1
unnamed: D8.1, K4_4.1
unnamed: D8.2, K3_4.1
unnamed: D2.3, D6.3, D10.2, K5_2.1
unnamed: D3.3, D7.3, D11.2, K5_3.1
unnamed: D12.1, D13.3
unnamed: D13.1, D14.3
unnamed: D14.1, D15.3
unnamed: D15.1, D16.3
unnamed: D16.1, D17.3
unnamed: D17.1, D18.3
unnamed: D18.1, D19.3
unnamed: D19.1, D20.3
unnamed: D20.1, D21.3
unnamed: D21.1, D22.3
unnamed: IC1.35, R7.2
unnamed: IC1.47, R8.1
unnamed: J1.2, R2.2
unnamed: J1.3, R3.2
unnamed: R1.2, U1.33
unnamed: R2.1, U1.3
unnamed: R3.1, U1.4
unnamed: R4.1, SW1.2, U1.13
Row1: K1_1.2, K1_2.2, K1_3.2, K1_4.2, U1.25
Row2: K2_1.2, K2_2.2, K2_3.2, K2_4.2, U1.26
Row3: K3_1.2, K3_2.2, K3_3.2, K3_4.2, U1.27
Row4: K4_1.2, K4_2.2, K4_3.2, K4_4.2, U1.28
Row5: K5_1.2, K5_2.2, K5_3.2, U1.29
VCC: C1.1, C2.1, C3.1, C4.1, C5.1, C9.1, C10.1, C11.1, C12.1, C13.1, C14.1, C15.1, C16.1, D13.4, D15.4, D17.4, D19.4, D21.4, D23.4, IC1.20, IC1.29, IC1.37, IC1.38, IC1.39, IC1.46, J1.1, R4.2, R5.1, R6.1, U1.2, U1.7, U1.14, U1.24, U1.34, U1.44

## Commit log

2018-10-16 Kicad Files added
2019-01-14 Version 1.0, sollte so gehen
2019-01-18 first manufactured version, testing needed
2019-01-19 rerouted D+ and D- lines
2019-02-06 Auf STM32F303 Controller umgestiegen. RGB per Switch rausgeflogen.
2019-03-02 USB war an falschem Pin. Fixed! Boot und Reset geaendert. Anderer Resetbutton
2019-04-20 - Quarz geaendert - Debug LED hinzugefügt

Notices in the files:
keypad.kicad_pcb:
©FM
